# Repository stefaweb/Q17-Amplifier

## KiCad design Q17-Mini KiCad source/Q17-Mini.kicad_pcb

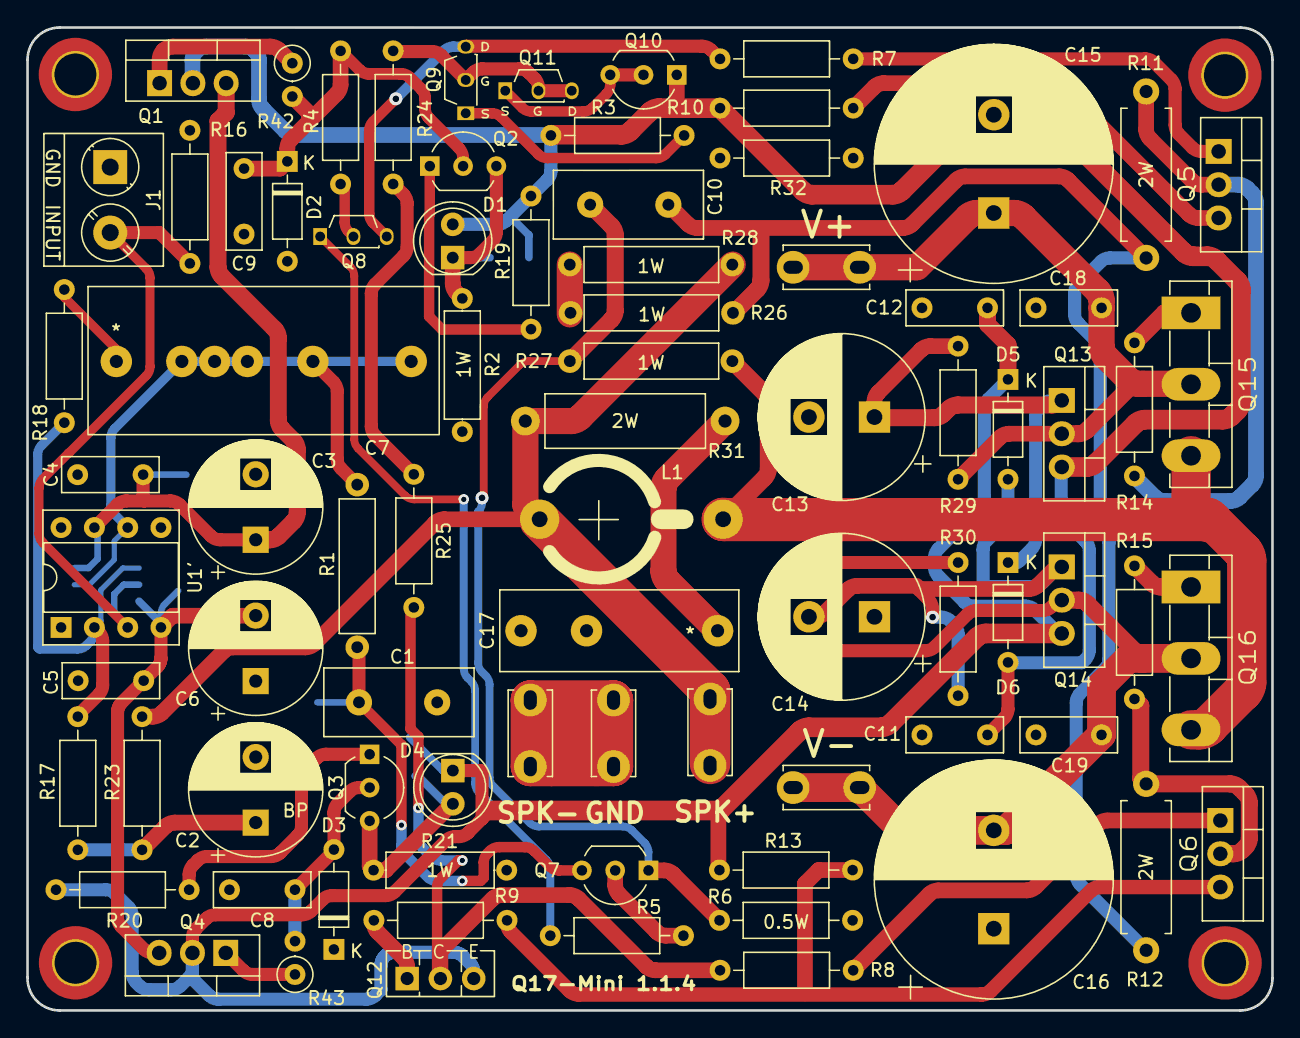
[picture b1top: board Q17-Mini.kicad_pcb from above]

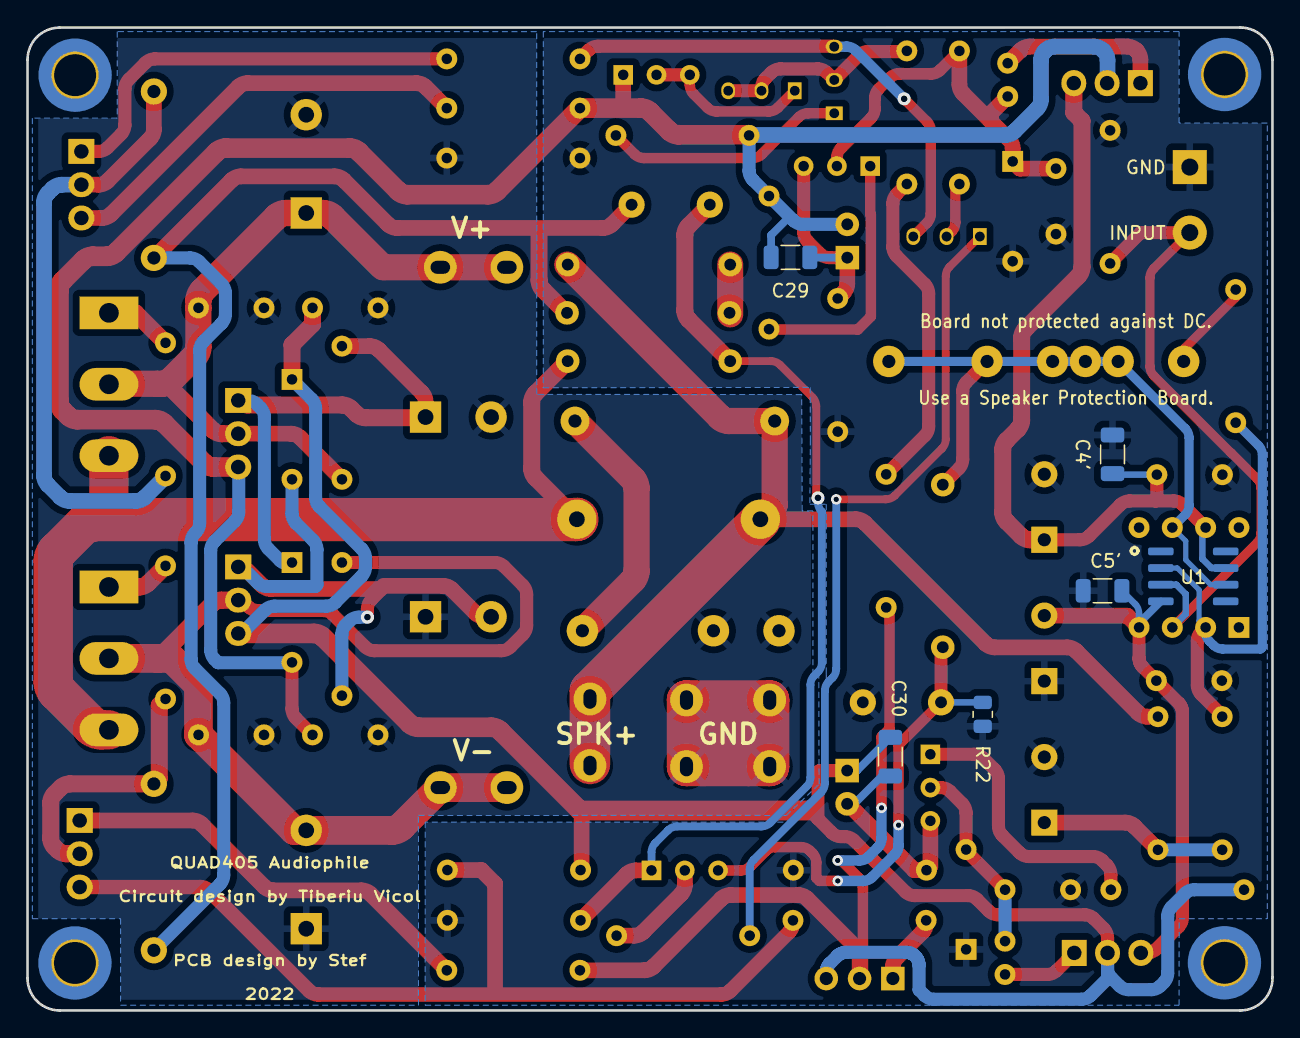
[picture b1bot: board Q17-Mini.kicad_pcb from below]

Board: 2 copper layers, 95.0 x 75.0 mm, 92 parts (6 on the bottom side), 48 nets.

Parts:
C1: 470p Mica; C_Mica_L11.4mm_W4.3mm_H9.1_P5.9mm
C2: 100uF/10V BP; CP_Radial_D10.0mm_P5.00mm
C3, C6: 100uF/16V; CP_Radial_D10.0mm_P5.00mm
C4, C5, C8, C9, C11, C12, C18, C19: 100nF; C_Rect_L7.2mm_W2.5mm_P5.00mm_FKS2_FKP2_MKS2_MKP2
C4', C5': 100nF; C_1206_3216Metric
C7: 1uF MKP; C_Rect_C7_Q17_Mini_L26.50_H11.00_P20.50
C10: 47pF Mica; C_Mica_L11.4mm_W4.3mm_H9.1_P5.9mm
C13, C14: 220uF/63V; CP_Radial_D12.5mm_P5.00mm
C15, C16: 2200uF/63V; CP_Radial_D18.0mm_P7.50mm
C17: 100nF MKP; C_Rect_L18.0mm_W6.0mm_P15.00mm_FKS3_FKP3
C29, C30: 100nF COG; C_1206_3216Metric
D1, D4: RED 2V; LED_D5.0mm
D2, D3: 1N5248B; D_DO-35_SOD27_P7.62mm_Horizontal
D5, D6: 1N5245B; D_DO-35_SOD27_P7.62mm_Horizontal
H1, H2, H4: MountingHole; MountingHole_3.2mm_M3_DIN965_Pad_TopBottom
H3: MountingHole_3.2mm_M3_DIN965_Pad_TopBottom
J1: Input; TerminalBlock_Phoenix_PT-1,5-2-5.0-H_1x02_P5.00mm_Horizontal
J2-1: SPK+; Faston_Connector_63849-1_TEC
J2-2: SPK-; Faston_Connector_63849-1_TEC
J3-1: V+; Faston_Connector_63849-1_TEC
J3-2: GND; Faston_Connector_63849-1_TEC
J3-3: V-; Faston_Connector_63849-1_TEC
L1: 1u2; L_Axial_L22mm_D10mm_P21mm_vertical_Q17_Mini
Q1, Q13: IRF610; TO-220-3_Vertical
Q2, Q10: KSA992; TO-92_Inline_Wide
Q3, Q7: KSC1845; TO-92_Inline_Wide
Q4, Q14: IRF9610; TO-220-3_Vertical
Q5: FQP3P20; TO-220-3_Vertical
Q6: FQP3N30; TO-220-3_Vertical
Q8: ZVN4206AV; TO-92S_Wide
Q9, Q11: ZVP2106A; TO-92S_Wide
Q12: BD139; TO-126-3_Vertical
Q15: FQA46N15; TO-3P-3_Vertical
Q16: FQA36P15; TO-3P-3_Vertical
R1: 2k7; R_Axial_L10.0mm_D3.50mm_P12.40mm_Horizontal
R2, R21: 5k6/1W; R_Axial_L8.0mm_D2.5mm_P10.16mm_Horizontal
R3: 150R; R_Axial_DIN0207_L6.3mm_D2.5mm_P10.16mm_Horizontal
R4, R7, R9, R29, R30: 100R; R_Axial_DIN0207_L6.3mm_D2.5mm_P10.16mm_Horizontal
R5, R10, R13, R32: 10R; R_Axial_DIN0207_L6.3mm_D2.5mm_P10.16mm_Horizontal
R6: 100R/0.5W; R_Axial_DIN0207_L6.3mm_D2.5mm_P10.16mm_Horizontal
R8: 120R; R_Axial_DIN0207_L6.3mm_D2.5mm_P10.16mm_Horizontal
R11, R12: 47R/2W; R_Axial_DIN0411_L9.9mm_D3.6mm_P12.70mm_Horizontal
R14, R15, R19, R20: 330R; R_Axial_DIN0207_L6.3mm_D2.5mm_P10.16mm_Horizontal
R16, R18: 22k; R_Axial_DIN0207_L6.3mm_D2.5mm_P10.16mm_Horizontal
R17: 7.32k; R_Axial_DIN0207_L6.3mm_D2.5mm_P10.16mm_Horizontal
R22: N.C; R_0805_2012Metric
R23, R24: 10k; R_Axial_DIN0207_L6.3mm_D2.5mm_P10.16mm_Horizontal
R25: 7k5; R_Axial_DIN0207_L6.3mm_D2.5mm_P10.16mm_Horizontal
R26, R28: 22R/1W; R_Axial_L10.0mm_D3.50mm_P12.40mm_Horizontal
R27: 560R/1W; R_Axial_L10.0mm_D3.50mm_P12.40mm_Horizontal
R31: 10R/2W; R_Axial_DIN0411_L9.9mm_D3.6mm_P15.24mm_Horizontal
R42, R43: 10R; R_Axial_DIN0207_L6.3mm_D2.5mm_P2.54mm_Vertical
U1: OPA1641; SOIC-8_3.9x4.9mm_P1.27mm
U1': OPA1641; DIP-8_W7.62mm_Socket

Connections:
GND: C1.2, C2.2, C3.2, C4.1, C4'.2, C5.1, C5'.2, C6.1, C8.1, C9.1, D2.2 (A), D3.1 (K), J1.1, R2.2, R6.2, R16.1, R21.2, R22.2, R32.1
GNDPWR: C11.1, C12.1, C13.2, C14.1, C15.2, C16.1, C17.2, C18.1, C19.2, J2-2.1, J3-2.1, R32.2
unnamed: C1.1, Q7.3 (B), R1.2, R22.1
unnamed: C2.1, R17.1, R23.1
unnamed: C3.1, C4.2, C4'.1, Q1.3 (S), U1.7 (V+), U1'.7 (V+)
unnamed: C5.2, C5'.1, C6.2, Q4.3 (S), U1.4 (V-), U1'.4 (V-)
unnamed: C7.1, R18.2
unnamed: C7.2, R1.1, U1.6, U1'.6
unnamed: C8.2, D3.2 (A), Q3.2 (C), R43.2
unnamed: C9.2, D2.1 (K), Q2.2 (C), R4.1, R42.2
unnamed: C10.1, R11.2, R12.1, R26.1
unnamed: C10.2, Q7.1 (E), R6.1, R27.1
unnamed: C11.2, C29.1, D1.2 (A), D6.2 (A), Q1.2 (D), Q10.1 (E), Q13.3 (S), R3.1, R10.1, R19.1
unnamed: C12.2, C30.2, D4.1 (K), D5.1 (K), Q4.2 (D), Q12.3 (E), Q14.3 (S), R13.2, R20.1
unnamed: C13.1, D6.1 (K), Q13.1 (G), R29.2
unnamed: C14.2, D5.2 (A), Q14.1 (G), R30.1
unnamed: C15.1, C18.2, J3-1.1, Q13.2 (D), Q15.2 (D), R29.1
unnamed: C16.2, C19.1, J3-3.1, Q14.2 (D), Q16.2 (D), R30.2
unnamed: C17.1, R31.2
unnamed: C29.2, D1.1 (K), Q2.3 (B), R2.1
unnamed: C30.1, D4.2 (A), Q3.3 (B), R21.1
unnamed: J1.2, R16.2, U1.3 (+), U1'.3 (+)
unnamed: J2-1.1, L1.1, R23.2, R28.2, R31.1
unnamed: L1.2, Q15.3 (S), Q16.3 (S), R27.2
unnamed: Q1.1 (G), R42.1
unnamed: Q2.1 (E), R19.2
unnamed: Q3.1 (E), R20.2
unnamed: Q4.1 (G), R43.1
unnamed: Q5.1 (G), R7.2
unnamed: Q5.2 (D), R11.1, R14.1
unnamed: Q5.3 (S), R10.2
unnamed: Q6.1 (G), R8.2
unnamed: Q6.2 (D), R12.2, R15.1
unnamed: Q6.3 (S), R9.2, R13.1
unnamed: Q7.2 (C), R5.2
unnamed: Q8.1 (S), R5.1
unnamed: Q8.2 (G), R4.2
unnamed: Q8.3 (D), Q9.3 (D), R7.1
unnamed: Q9.1 (S), R3.2
unnamed: Q10.2 (C), Q10.3 (B), Q11.1 (S)
unnamed: Q9.2 (G), Q11.2 (G), Q11.3 (D), R24.1
unnamed: Q12.1 (B), R9.1
unnamed: Q12.2 (C), R8.1, R25.2
unnamed: Q15.1 (G), R14.2
unnamed: Q16.1 (G), R15.2
unnamed: R17.2, R18.1, U1.2 (-), U1'.2 (-)
unnamed: R24.2, R25.1
unnamed: R26.2, R28.1

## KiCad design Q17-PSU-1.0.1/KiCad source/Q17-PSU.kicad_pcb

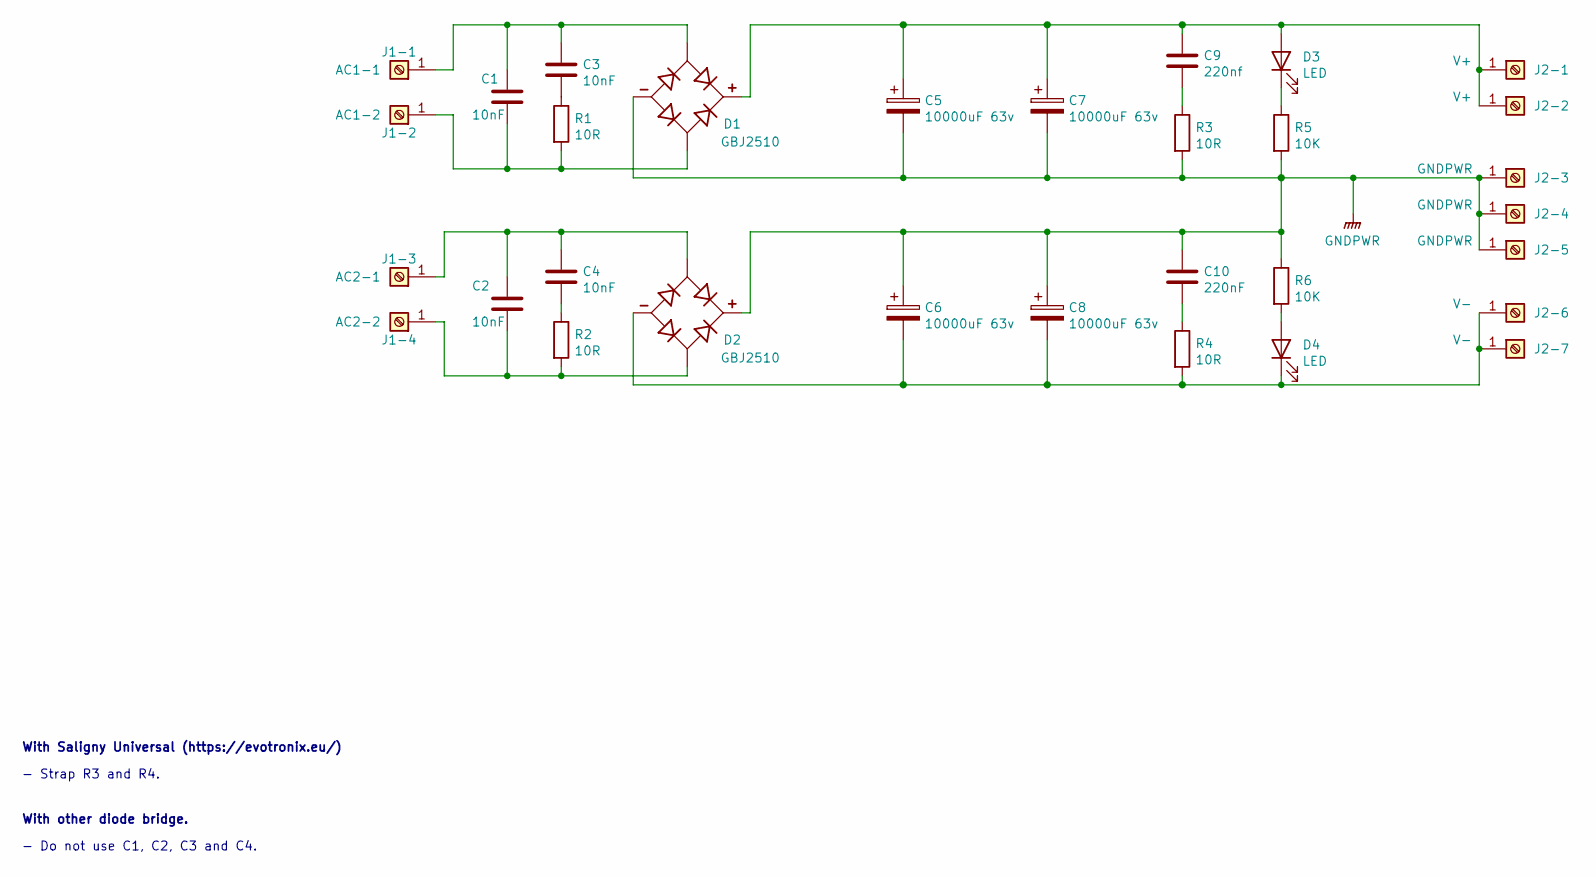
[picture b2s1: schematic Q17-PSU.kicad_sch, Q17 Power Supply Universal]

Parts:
C1, C2: 10nF; C_Rect_L10.0mm_W4.0mm_P7.50mm_MKS4; Part# MKP1G021002C00KF00; Mouser 505-MKP1G021002C00KF
C3, C4: 10nF; C_Rect_L13.0mm_W5.0mm_P10.00mm_FKS3_FKP3_MKS4; Part# MPX103K305D; Mouser 598-MPX103K305D
C5, C6, C7, C8: 10000uF 63v; CP_Radial_D35.0mm_P10.00mm_SnapIn; Part# 861020786030; Mouser 710-861020786030
C9: 220nf; C_Rect_L18.0mm_W8.0mm_P15.00mm_FKS3_FKP3; Part# MPX224K305E; Mouser 598-MPX224K305E
C10: 220nF; C_Rect_L18.0mm_W8.0mm_P15.00mm_FKS3_FKP3; Part# MPX224K305E; Mouser 598-MPX224K305E
D1, D2: GBJ2510; DIOB_GBJ2510; Part# GSIB2580-E3/45; Mouser 625-GSIB2580-E3
D3, D4: LED; LED_D5.0mm; Part# TLHR5400; Mouser 78-TLHR5400
J1-1: AC1-1; Faston_Connector_63849-1_TEC; Part# TE Connectivity 63849-1; Mouser 571-638241
J1-2: AC1-2; Faston_Connector_63849-1_TEC; Part# TE Connectivity 63849-1; Mouser 571-638241
J1-3: AC2-1; Faston_Connector_63849-1_TEC; Part# TE Connectivity 63849-1; Mouser 571-638241
J1-4: AC2-2; Faston_Connector_63849-1_TEC; Part# TE Connectivity 63849-1; Mouser 571-638241
J2-1, J2-2: V+; Faston_Connector_63849-1_TEC; Part# TE Connectivity 63849-1; Mouser 571-638241
J2-3, J2-4, J2-5: GNDPWR; Faston_Connector_63849-1_TEC; Part# TE Connectivity 63849-1; Mouser 571-638241
J2-6, J2-7: V-; Faston_Connector_63849-1_TEC; Part# TE Connectivity 63849-1; Mouser 571-638241
R1, R2, R3, R4: 10R; R_Axial_DIN0207_L6.3mm_D2.5mm_P10.16mm_Horizontal; Part# MRS25000C1009FRP00; Mouser 594-MRS25000C1009FRP
R5: 10K; R_Axial_DIN0207_L6.3mm_D2.5mm_P10.16mm_Horizontal; Part# PR01000101002JR500; Mouser 594-5073NW10K00J
R6: 10K; R_Axial_DIN0207_L6.3mm_D2.5mm_P10.16mm_Horizontal; Part# 594-5073NW10K00J; Mouser PR01000101002JR500

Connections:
GNDPWR: C5.2, C6.1, C7.2, C8.1, C10.1, D1.4, D2.1, J2-3.1, J2-4.1, J2-5.1, R3.2, R5.2, R6.1
unnamed: C3.2, R1.1
unnamed: C4.2, R2.1
unnamed: C9.2, R3.1
unnamed: C10.2, R4.1
unnamed: C5.1, C7.1, C9.1, D1.1, D3.2 (A), J2-1.1, J2-2.1
unnamed: D3.1 (K), R5.1
unnamed: D4.2 (A), R6.2
unnamed: C6.2, C8.2, D2.4, D4.1 (K), J2-6.1, J2-7.1, R4.2
unnamed: C1.1, C3.1, D1.2, J1-1.1
unnamed: C1.2, D1.3, J1-2.1, R1.2
unnamed: C2.1, C4.1, D2.2, J1-3.1
unnamed: C2.2, D2.3, J1-4.1, R2.2

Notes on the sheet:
- Strap R3 and R4.
With Saligny Universal (https://evotronix.eu/)
With other diode bridge.
- Do not use C1, C2, C3 and C4.

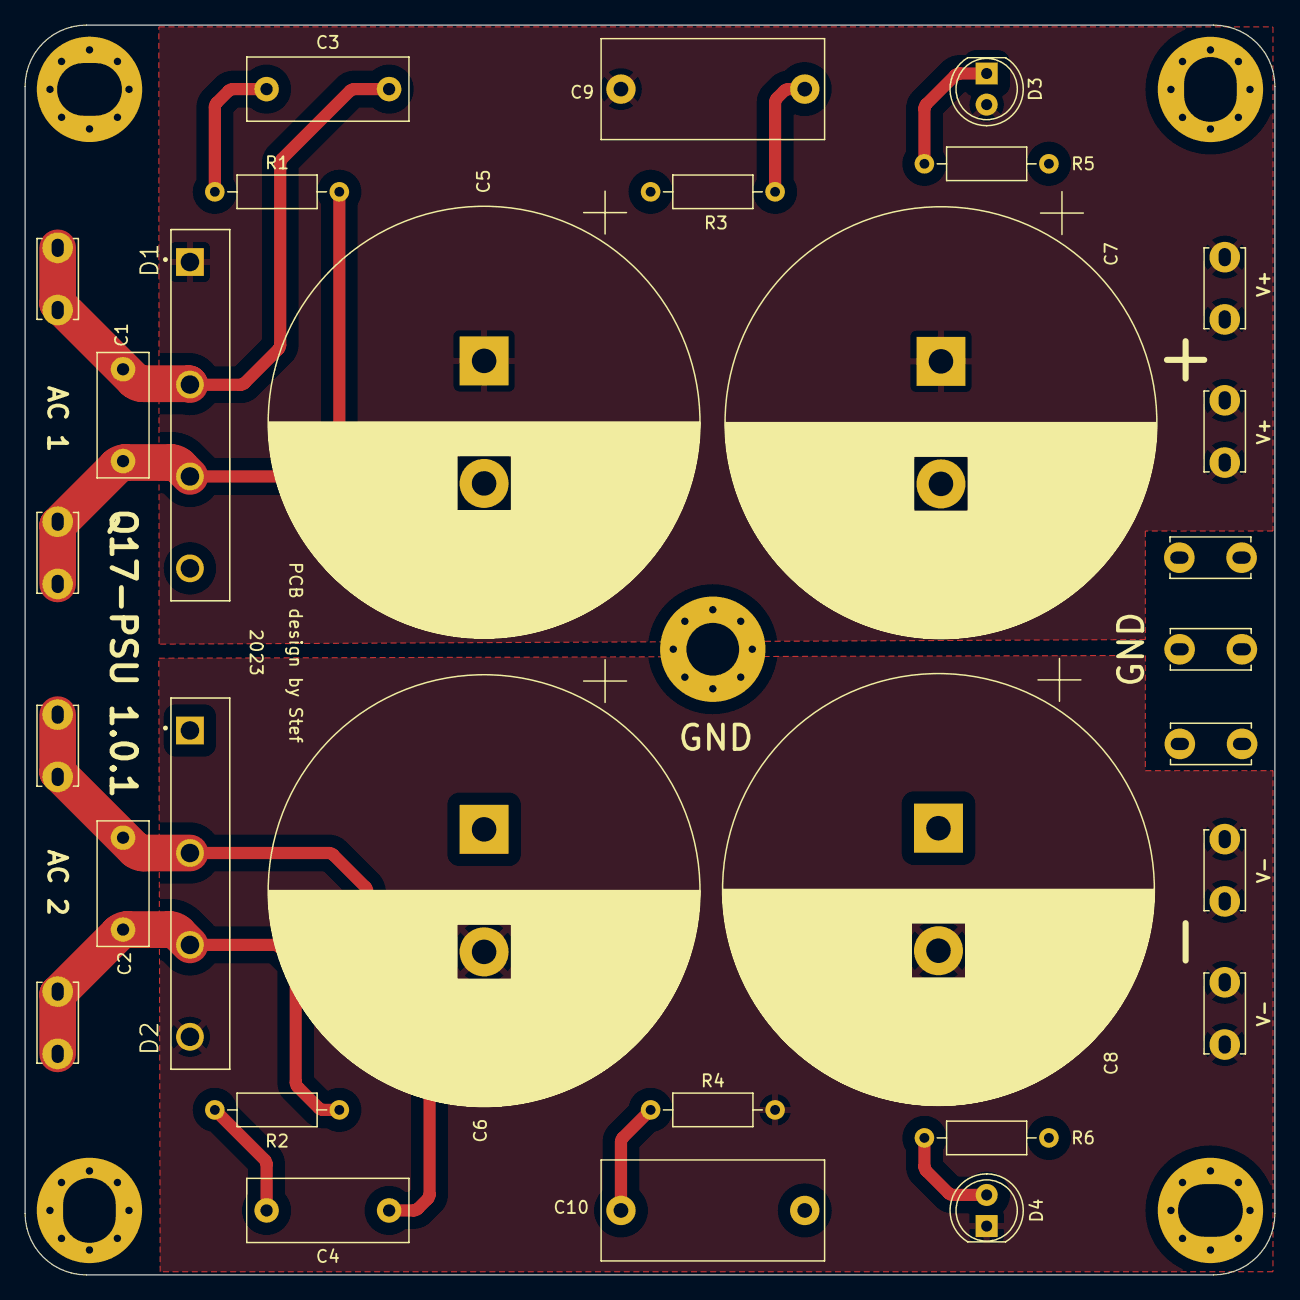
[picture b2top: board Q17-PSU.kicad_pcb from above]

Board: 2 copper layers, 102.0 x 102.0 mm, 31 parts (0 on the bottom side), 13 nets.
